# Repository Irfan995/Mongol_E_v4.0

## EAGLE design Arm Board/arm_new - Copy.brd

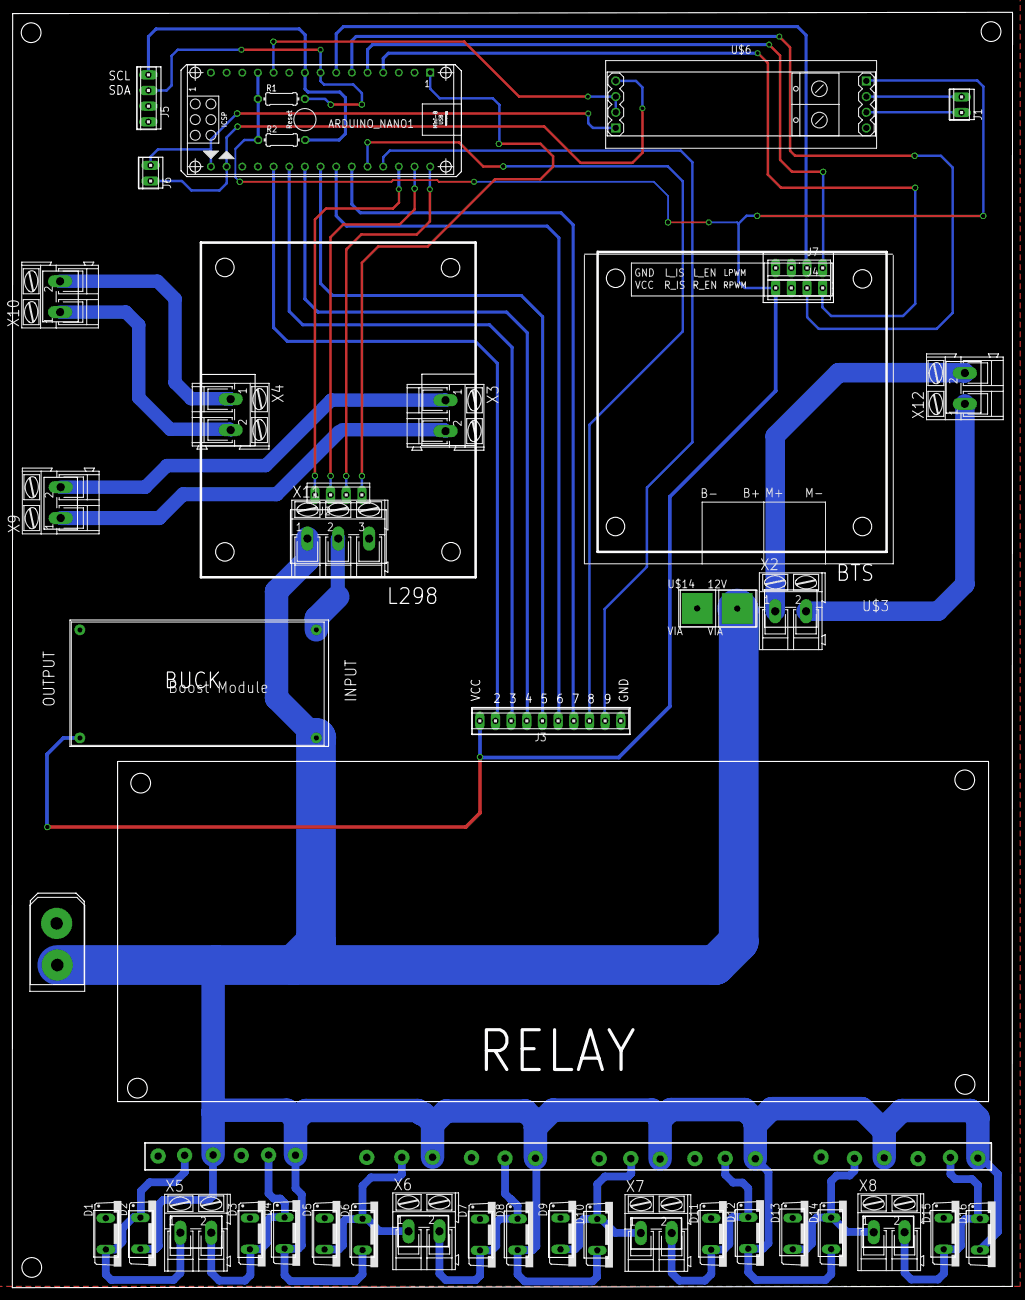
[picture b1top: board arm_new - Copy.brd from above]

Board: 2 copper layers, 162.2 x 206.8 mm, 68 parts (0 on the bottom side), 40 nets.

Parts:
12V: VIA
ARDUINO_NANO1: ARDUINO_NANO
D1, D2, D3, D4, D5, D6, D7, D8, D9, D10, D11, D12, D13, D14, D15, D16: MUR810; TO220ACS
J1, J6: 10X02MTA
J2, J4, J5, J7: 10X04MTA
J3: 10X10MTA
NO, NO1, NO2, NO3: NO; ROUND_VIA
R1, R2: 4.7K; 0204/7
U$1: BOOST_MODULE
U$2: XT60; CONNECTOR
U$3: IBT-2
U$4: L298
U$6: RS485-TTL-CONVERTER
U$14: VIA
U$17, U$18, U$19, U$20, U$21, U$22, U$23, U$24, U$25, U$26, U$27, U$28, U$29, U$30, U$31, U$32, U$33, U$34, U$35, U$36: ROUND_VIA
X2, X3, X4, X5, X6, X7, X8, X9, X10, X12: AK300/2
X11: AK300/3

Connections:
5V: ARDUINO_NANO1.12, J3.10, J4.1, R1.1, R2.1, U$1.OUT+, U$6.J2.1
GND: ARDUINO_NANO1.14, ARDUINO_NANO1.19, D1.C, D3.C, D5.C, D7.C, D9.C, D11.C, D13.C, D15.C, J3.1, J5.3, J7.1, NO.P$1, NO1.P$1, NO2.P$1, NO3.P$1, U$1.IN-, U$1.OUT-, U$2.P$1, U$6.J2.4, U$14.P$1, U$20.P$1, U$24.P$1, U$29.P$1, U$34.P$1, X11.2
unnamed: ARDUINO_NANO1.6, J4.3
unnamed: ARDUINO_NANO1.4, J4.4
unnamed: ARDUINO_NANO1.7, J7.3
unnamed: ARDUINO_NANO1.5, J7.4
unnamed: X3.2, X9.1
unnamed: X4.1, X10.2
unnamed: X4.2, X10.1
unnamed: ARDUINO_NANO1.1, J2.1
unnamed: D1.A, D2.C, U$18.P$1, X5.1
unnamed: ARDUINO_NANO1.30, J2.2
unnamed: ARDUINO_NANO1.20, J3.9
unnamed: ARDUINO_NANO1.29, J2.3
unnamed: ARDUINO_NANO1.28, J2.4
unnamed: ARDUINO_NANO1.21, J3.8
unnamed: ARDUINO_NANO1.22, J3.7
unnamed: D5.A, D6.C, U$17.P$1, X6.1
unnamed: ARDUINO_NANO1.23, J3.6
unnamed: ARDUINO_NANO1.24, J3.5
unnamed: ARDUINO_NANO1.25, J3.4
unnamed: ARDUINO_NANO1.26, J3.3
unnamed: ARDUINO_NANO1.27, J3.2
unnamed: ARDUINO_NANO1.16, J6.1, U$6.J1.1
unnamed: J1.1, U$6.J2.2
unnamed: ARDUINO_NANO1.9, J5.1, R2.2
unnamed: ARDUINO_NANO1.8, J5.2, R1.2
unnamed: D9.A, D10.C, U$27.P$1, X7.1
unnamed: D3.A, D4.C, U$21.P$1, X5.2
unnamed: D7.A, D8.C, U$25.P$1, X6.2
unnamed: D13.A, D14.C, U$32.P$1, X8.1
unnamed: D11.A, D12.C, U$30.P$1, X7.2
unnamed: 12V.P$1, D2.A, D4.A, D6.A, D8.A, D10.A, D12.A, D14.A, D16.A, U$1.IN+, U$2.P$2, U$19.P$1, U$22.P$1, U$23.P$1, U$26.P$1, U$28.P$1, U$31.P$1, U$33.P$1, U$36.P$1, X11.1
unnamed: D15.A, D16.C, U$35.P$1, X8.2
unnamed: X3.1, X9.2
unnamed: ARDUINO_NANO1.17, J6.2, U$6.J1.4
unnamed: ARDUINO_NANO1.11, U$6.J1.2, U$6.J1.3
unnamed: J1.2, U$6.J2.3
unnamed: X2.1, X12.2
unnamed: X2.2, X12.1

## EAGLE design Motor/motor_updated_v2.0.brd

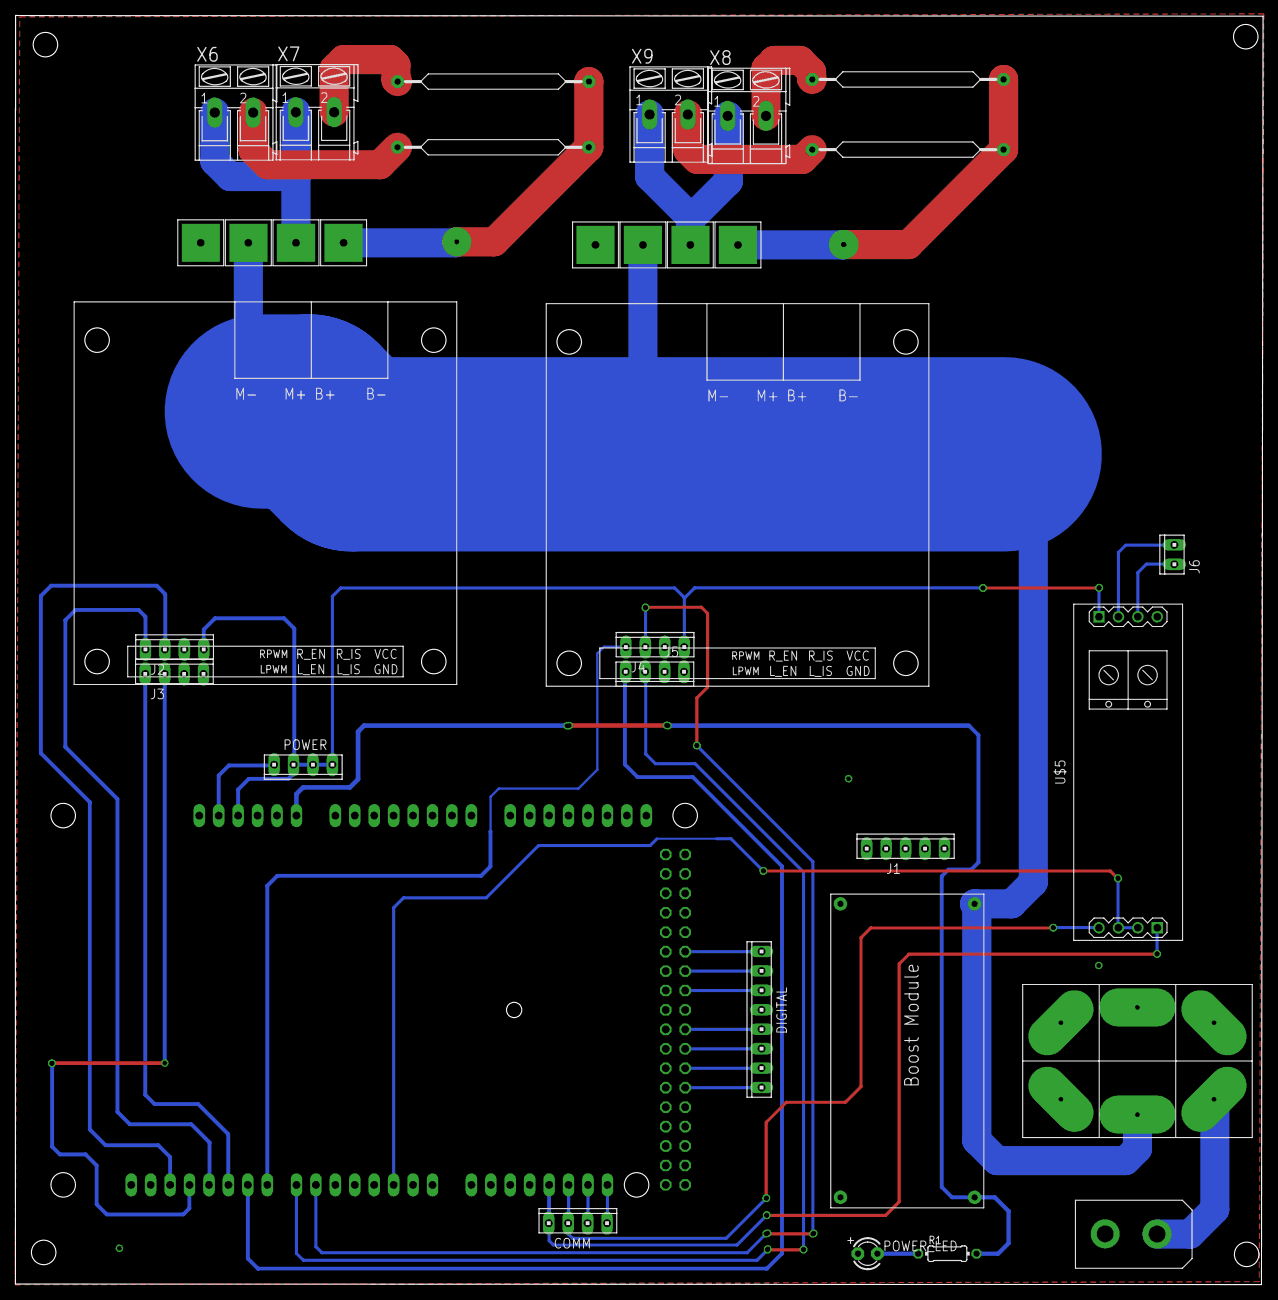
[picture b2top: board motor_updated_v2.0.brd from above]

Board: 2 copper layers, 163.0 x 165.9 mm, 34 parts (1 on the bottom side), 38 nets.

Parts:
COMM: 10X04MTA
DIGITAL: 10X08MTA
IC1: MEGA_ARDUINO
J1: GND\; 10X05MTA
J2, J3, J4, J5: 10X04MTA
J6: 10X02MTA
POWER: 10X04MTA
POWER_LED: LED3MM
R1: 0204/7
U$1: BOOST_MODULE
U$2: XT60; CONNECTOR
U$3, U$4: IBT-2
U$5: RS485-TTL-CONVERTER
U$6, U$8, U$9, U$12, U$13, U$14, U$15, U$23: VIA
U$18, U$19, U$20, U$21: FUSE_MINE
U$24: SWITCH; TOGGLE
X6, X7, X8, X9: AK300/2

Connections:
+5V: IC1.47, IC1.48
GND: IC1.4, IC1.5, IC1.45, IC1.81, IC1.82, J1.1, J1.2, J1.3, J1.4, J1.5, J3.1, J5.4, POWER_LED.A, U$1.IN-, U$1.OUT-, U$2.P$2, U$5.J2.4, U$6.P$1, U$9.P$1, U$24.P$2, U$24.P$5
unnamed: IC1.6, R1.2, U$1.OUT+
unnamed: COMM.1, IC1.23
unnamed: U$2.P$1, U$24.P$3
unnamed: COMM.2, IC1.24
unnamed: COMM.3, IC1.25, U$5.J1.4
unnamed: COMM.4, IC1.26, U$5.J1.1
unnamed: IC1.2, POWER.1
unnamed: DIGITAL.8, IC1.58
unnamed: IC1.39, J4.4
unnamed: IC1.33, U$5.J1.2, U$5.J1.3
unnamed: U$1.IN+, U$8.P$1, U$23.P$1, U$24.P$1
unnamed: J6.2, U$5.J2.3
unnamed: POWER_LED.K, R1.1
unnamed: J6.1, U$5.J2.2
unnamed: DIGITAL.7, IC1.60
unnamed: DIGITAL.5, IC1.64
unnamed: DIGITAL.3, IC1.68
unnamed: DIGITAL.2, IC1.70
unnamed: DIGITAL.1, IC1.72
unnamed: U$12.P$1, X6.1, X7.1
unnamed: U$13.P$1, U$18.P$2, U$19.P$1
unnamed: U$14.P$1, X8.1, X9.1
unnamed: U$15.P$1, U$20.P$2, U$21.P$1
unnamed: IC1.44, J2.3
unnamed: DIGITAL.6, IC1.62
unnamed: IC1.43, J3.3
unnamed: IC1.37, J4.3
unnamed: IC1.38, J5.2
unnamed: IC1.42, J2.4
unnamed: IC1.41, J3.4
unnamed: U$19.P$2, X7.2
unnamed: IC1.40, J5.1
unnamed: U$18.P$1, X6.2
unnamed: U$21.P$2, X9.2
unnamed: U$20.P$1, X8.2
POWER: IC1.3, J2.1, J4.1, POWER.2, POWER.3, POWER.4, U$5.J2.1

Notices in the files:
parts and their libraries:
diy-modules: Released under the Creative Commons Attribution 4.0 International License: http://creativecommons.org/licenses/by/4.0
